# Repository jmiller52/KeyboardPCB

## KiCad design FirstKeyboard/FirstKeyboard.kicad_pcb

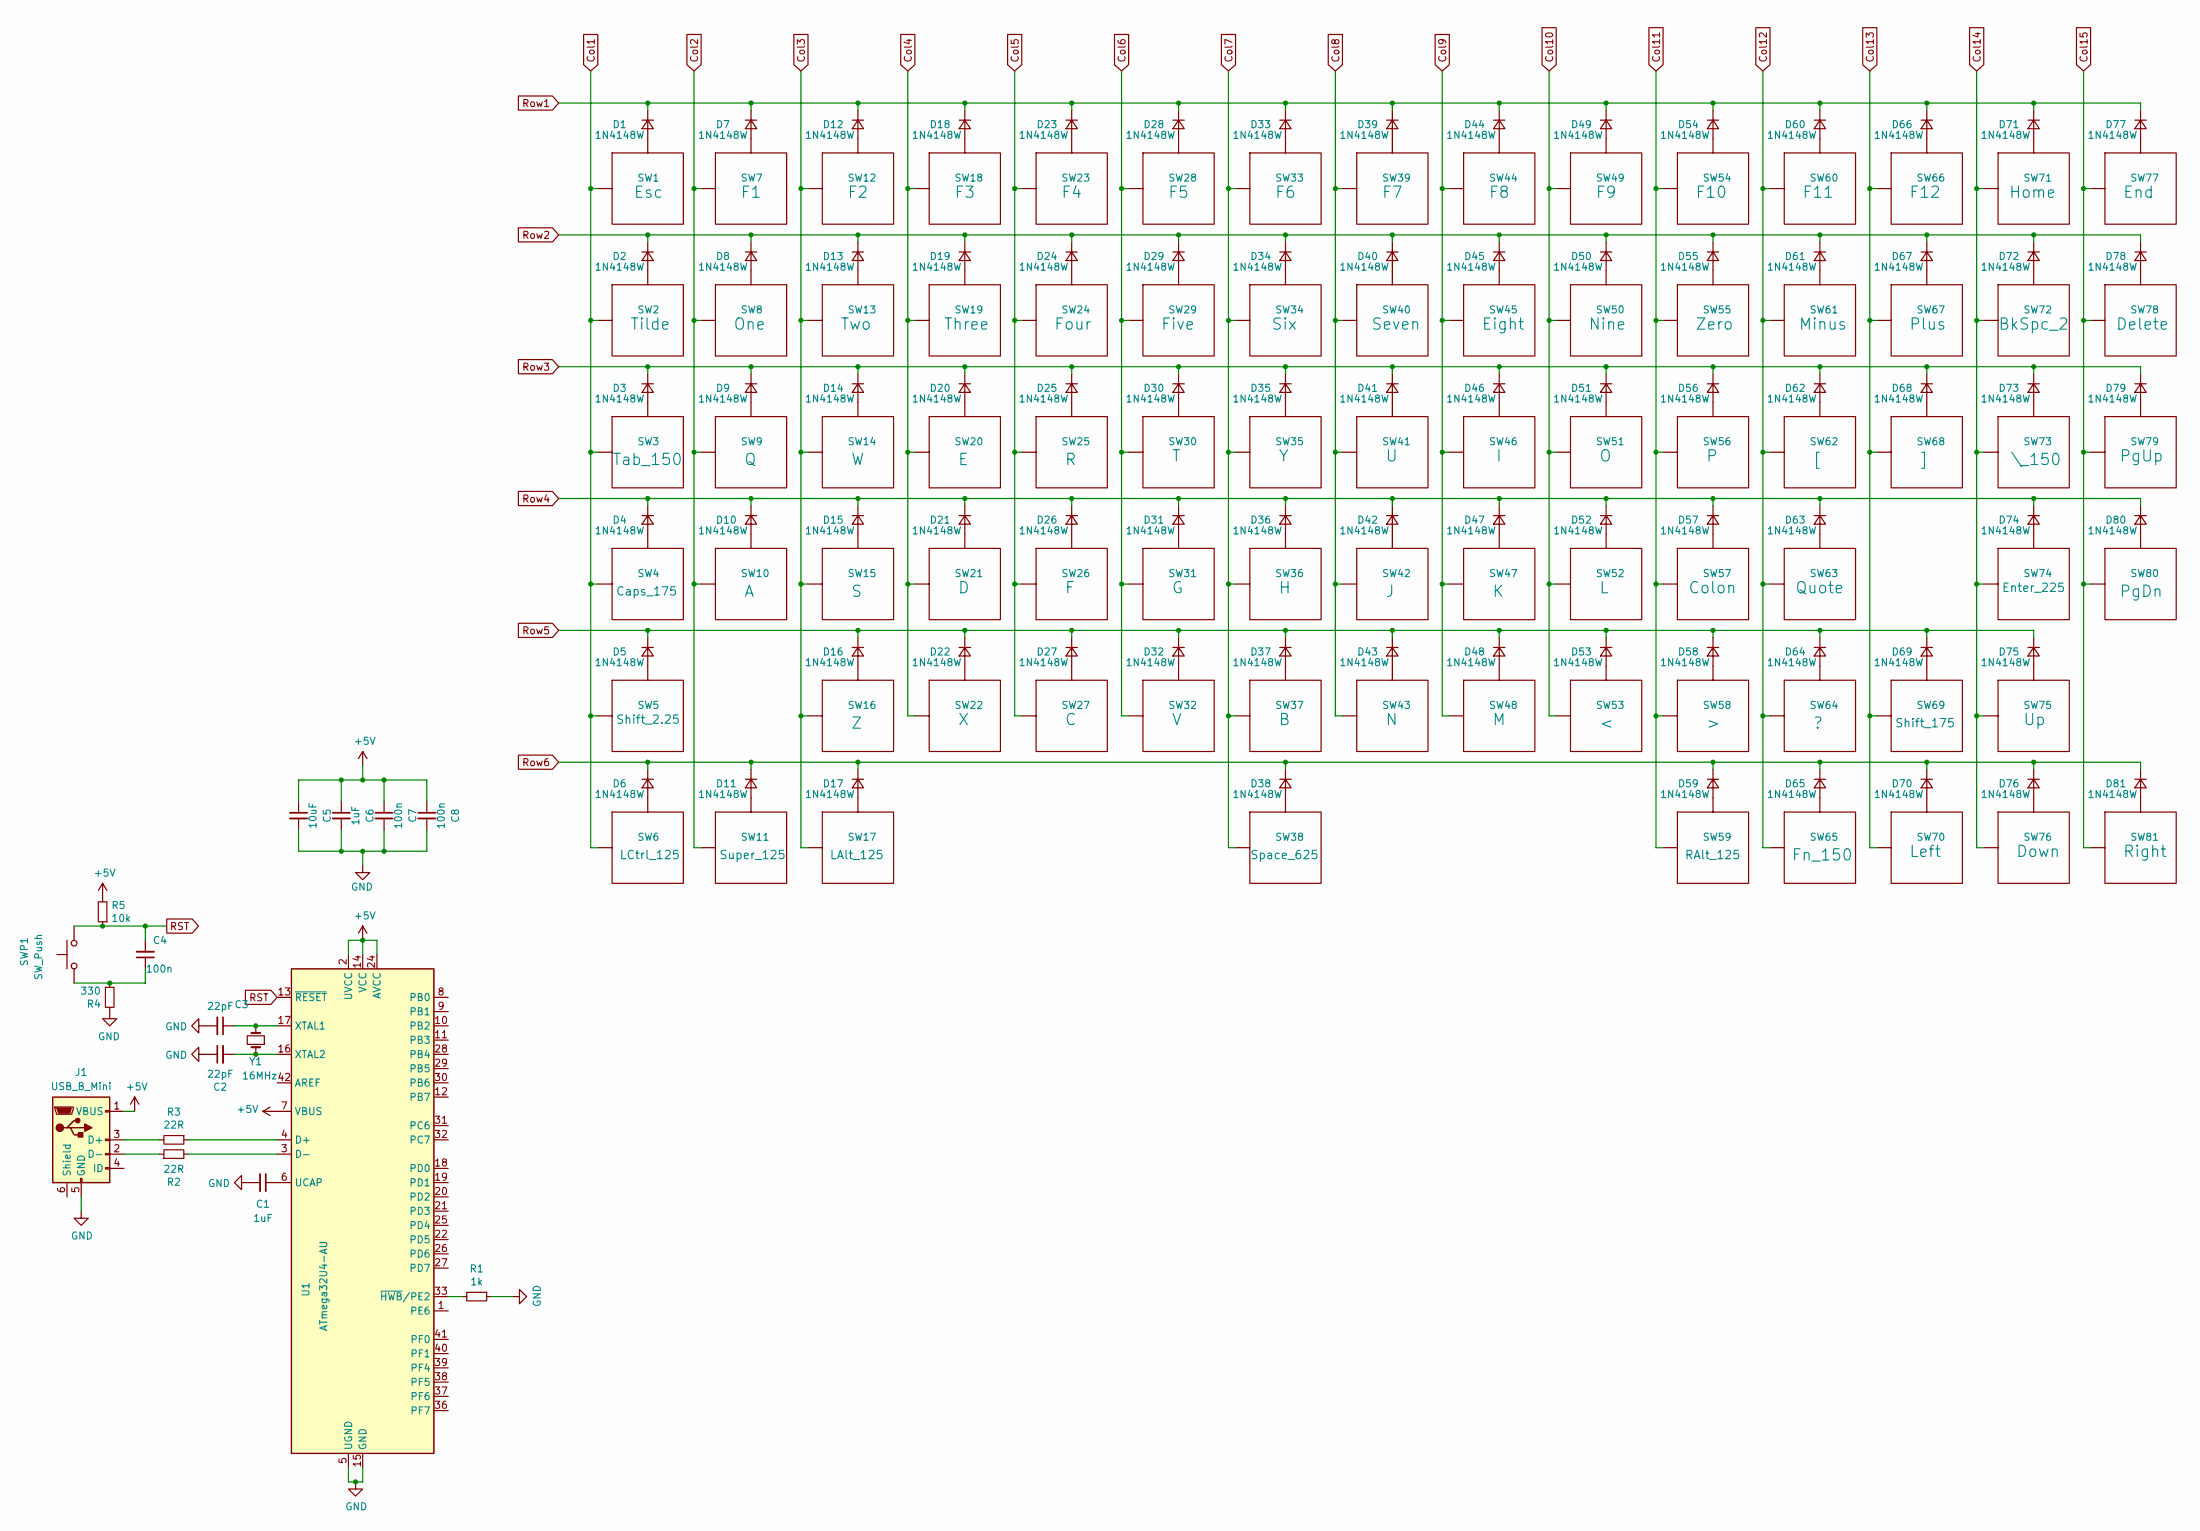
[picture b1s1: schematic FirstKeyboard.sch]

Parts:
C1, C6: 1uF; C_0805_2012Metric_Pad1.15x1.40mm_HandSolder
C2, C3: 22pF; C_0805_2012Metric_Pad1.15x1.40mm_HandSolder
C4, C7, C8: 100n; C_0805_2012Metric_Pad1.15x1.40mm_HandSolder
C5: 10uF; C_0805_2012Metric_Pad1.15x1.40mm_HandSolder
D1, D2, D3, D4, D5, D6, D7, D8, D9, D10, D11, D12, D13, D14, D15, D16, D17, D18, D19, D20, D21, D22, D23, D24, D25, D26, D27, D28, D29, D30, D31, D32, D33, D34, D35, D36, D37, D38, D39, D40, D41, D42, D43, D44, D45, D46, D47, D48, D49, D50, D51, D52, D53, D54, D55, D56, D57, D58, D59, D60, D61, D62, D63, D64, D65, D66, D67, D68, D69, D70, D71, D72, D73, D74, D75, D76, D77, D78, D79, D80, D81: 1N4148W; D_SOD-123
J1: USB_B_Mini; USB_MiniB_XM7D-0512
R1: 1k; R_1206_3216Metric_Pad1.42x1.75mm_HandSolder
R2, R3: 22R; R_1206_3216Metric_Pad1.42x1.75mm_HandSolder
R4: 330; R_1206_3216Metric_Pad1.42x1.75mm_HandSolder
R5: 10k; R_1206_3216Metric_Pad1.42x1.75mm_HandSolder
SW1: Esc; MX100P
SW2: Tilde; MX100P
SW3: Tab_150; MX150P
SW4: Caps_175; MX175P
SW5: Shift_2.25; MX225P
SW6: LCtrl_125; MX125P
SW7: F1; MX100P
SW8: One; MX100P
SW9: Q; MX100P
SW10: A; MX100P
SW11: Super_125; MX125P
SW12: F2; MX100P
SW13: Two; MX100P
SW14: W; MX100P
SW15: S; MX100P
SW16: Z; MX100P
SW17: LAlt_125; MX125P
SW18: F3; MX100P
SW19: Three; MX100P
SW20: E; MX100P
SW21: D; MX100P
SW22: X; MX100P
SW23: F4; MX100P
SW24: Four; MX100P
SW25: R; MX100P
SW26: F; MX100P
SW27: C; MX100P
SW28: F5; MX100P
SW29: Five; MX100P
SW30: T; MX100P
SW31: G; MX100P
SW32: V; MX100P
SW33: F6; MX100P
SW34: Six; MX100P
SW35: Y; MX100P
SW36: H; MX100P
SW37: B; MX100P
SW38: Space_625; MX625P
SW39: F7; MX100P
SW40: Seven; MX100P
SW41: U; MX100P
SW42: J; MX100P
SW43: N; MX100P
SW44: F8; MX100P
SW45: Eight; MX100P
SW46: I; MX100P
SW47: K; MX100P
SW48: M; MX100P
SW49: F9; MX100P
SW50: Nine; MX100P
SW51: O; MX100P
SW52: L; MX100P
SW53: <; MX100P
SW54: F10; MX100P
SW55: Zero; MX100P
SW56: P; MX100P
SW57: Colon; MX100P
SW58: >; MX100P
SW59: RAlt_125; MX125P
SW60: F11; MX100P
SW61: Minus; MX100P
SW62: [; MX100P
SW63: Quote; MX100P
SW64: ?; MX100P
SW65: Fn_150; MX150P
SW66: F12; MX100P
SW67: Plus; MX100P
SW68: ]; MX100P
SW69: Shift_175; MX175P
SW70: Left; MX100P
SW71: Home; MX100P
SW72: BkSpc_2; MX200P
SW73: \\_150; MX150P
SW74: Enter_225; MX225P
SW75: Up; MX100P
SW76: Down; MX100P
SW77: End; MX100P
SW78: Delete; MX100P
SW79: PgUp; MX100P
SW80: PgDn; MX100P
SW81: Right; MX100P
SWP1: SW_Push; smdPushBtn
U1: ATmega32U4-AU; TQFP-44_10x10mm_P0.8mm
Y1: 16MHz; Crystal_SMD_5032-2Pin_5.0x3.2mm_HandSoldering

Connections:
+5V: C5.1, C6.1, C7.1, C8.1, J1.1 (VBUS), R5.2, U1.2 (UVCC), U1.7 (VBUS), U1.14 (VCC), U1.24 (AVCC), U1.34 (VCC), U1.44 (AVCC)
Col1: SW1.1 (Col), SW2.1 (Col), SW3.1 (Col), SW4.1 (Col), SW5.1 (Col), SW6.1 (Col)
Col2: SW7.1 (Col), SW8.1 (Col), SW9.1 (Col), SW10.1 (Col), SW11.1 (Col)
Col3: SW12.1 (Col), SW13.1 (Col), SW14.1 (Col), SW15.1 (Col), SW16.1 (Col), SW17.1 (Col)
Col4: SW18.1 (Col), SW19.1 (Col), SW20.1 (Col), SW21.1 (Col), SW22.1 (Col)
Col5: SW23.1 (Col), SW24.1 (Col), SW25.1 (Col), SW26.1 (Col), SW27.1 (Col)
Col6: SW28.1 (Col), SW29.1 (Col), SW30.1 (Col), SW31.1 (Col), SW32.1 (Col)
Col7: SW33.1 (Col), SW34.1 (Col), SW35.1 (Col), SW36.1 (Col), SW37.1 (Col), SW38.1 (Col)
Col8: SW39.1 (Col), SW40.1 (Col), SW41.1 (Col), SW42.1 (Col), SW43.1 (Col)
Col9: SW44.1 (Col), SW45.1 (Col), SW46.1 (Col), SW47.1 (Col), SW48.1 (Col)
Col10: SW49.1 (Col), SW50.1 (Col), SW51.1 (Col), SW52.1 (Col), SW53.1 (Col)
Col11: SW54.1 (Col), SW55.1 (Col), SW56.1 (Col), SW57.1 (Col), SW58.1 (Col), SW59.1 (Col)
Col12: SW60.1 (Col), SW61.1 (Col), SW62.1 (Col), SW63.1 (Col), SW64.1 (Col), SW65.1 (Col)
Col13: SW66.1 (Col), SW67.1 (Col), SW68.1 (Col), SW69.1 (Col), SW70.1 (Col)
Col14: SW71.1 (Col), SW72.1 (Col), SW73.1 (Col), SW74.1 (Col), SW75.1 (Col), SW76.1 (Col)
Col15: SW77.1 (Col), SW78.1 (Col), SW79.1 (Col), SW80.1 (Col), SW81.1 (Col)
GND: C1.2, C2.1, C3.2, C5.2, C6.2, C7.2, C8.2, J1.5 (GND), R1.1, R4.2, U1.5 (UGND), U1.15 (GND), U1.23 (GND), U1.35 (GND), U1.43 (GND)
unnamed: C1.1, U1.6 (UCAP)
unnamed: C2.2, U1.16 (XTAL2), Y1.1
unnamed: C3.1, U1.17 (XTAL1), Y1.2
unnamed: C4.1, R4.1, SWP1.1
unnamed: D1.2 (A), SW1.2 (Row)
unnamed: D2.2 (A), SW2.2 (Row)
unnamed: D3.2 (A), SW3.2 (Row)
unnamed: D4.2 (A), SW4.2 (Row)
unnamed: D5.2 (A), SW5.2 (Row)
unnamed: D6.2 (A), SW6.2 (Row)
unnamed: D7.2 (A), SW7.2 (Row)
unnamed: D8.2 (A), SW8.2 (Row)
unnamed: D9.2 (A), SW9.2 (Row)
unnamed: D10.2 (A), SW10.2 (Row)
unnamed: D11.2 (A), SW11.2 (Row)
unnamed: D12.2 (A), SW12.2 (Row)
unnamed: D13.2 (A), SW13.2 (Row)
unnamed: D14.2 (A), SW14.2 (Row)
unnamed: D15.2 (A), SW15.2 (Row)
unnamed: D16.2 (A), SW16.2 (Row)
unnamed: D17.2 (A), SW17.2 (Row)
unnamed: D18.2 (A), SW18.2 (Row)
unnamed: D19.2 (A), SW19.2 (Row)
unnamed: D20.2 (A), SW20.2 (Row)
unnamed: D21.2 (A), SW21.2 (Row)
unnamed: D22.2 (A), SW22.2 (Row)
unnamed: D23.2 (A), SW23.2 (Row)
unnamed: D24.2 (A), SW24.2 (Row)
unnamed: D25.2 (A), SW25.2 (Row)
unnamed: D26.2 (A), SW26.2 (Row)
unnamed: D27.2 (A), SW27.2 (Row)
unnamed: D28.2 (A), SW28.2 (Row)
unnamed: D29.2 (A), SW29.2 (Row)
unnamed: D30.2 (A), SW30.2 (Row)
unnamed: D31.2 (A), SW31.2 (Row)
unnamed: D32.2 (A), SW32.2 (Row)
unnamed: D33.2 (A), SW33.2 (Row)
unnamed: D34.2 (A), SW34.2 (Row)
unnamed: D35.2 (A), SW35.2 (Row)
unnamed: D36.2 (A), SW36.2 (Row)
unnamed: D37.2 (A), SW37.2 (Row)
unnamed: D38.2 (A), SW38.2 (Row)
unnamed: D39.2 (A), SW39.2 (Row)
unnamed: D40.2 (A), SW40.2 (Row)
unnamed: D41.2 (A), SW41.2 (Row)
unnamed: D42.2 (A), SW42.2 (Row)
unnamed: D43.2 (A), SW43.2 (Row)
unnamed: D44.2 (A), SW44.2 (Row)
unnamed: D45.2 (A), SW45.2 (Row)
unnamed: D46.2 (A), SW46.2 (Row)
unnamed: D47.2 (A), SW47.2 (Row)
unnamed: D48.2 (A), SW48.2 (Row)
unnamed: D49.2 (A), SW49.2 (Row)
unnamed: D50.2 (A), SW50.2 (Row)
unnamed: D51.2 (A), SW51.2 (Row)
unnamed: D52.2 (A), SW52.2 (Row)
unnamed: D53.2 (A), SW53.2 (Row)
unnamed: D54.2 (A), SW54.2 (Row)
unnamed: D55.2 (A), SW55.2 (Row)
unnamed: D56.2 (A), SW56.2 (Row)
unnamed: D57.2 (A), SW57.2 (Row)
unnamed: D58.2 (A), SW58.2 (Row)
unnamed: D59.2 (A), SW59.2 (Row)
unnamed: D60.2 (A), SW60.2 (Row)
unnamed: D61.2 (A), SW61.2 (Row)
unnamed: D62.2 (A), SW62.2 (Row)
unnamed: D63.2 (A), SW63.2 (Row)
unnamed: D64.2 (A), SW64.2 (Row)
unnamed: D65.2 (A), SW65.2 (Row)
unnamed: D66.2 (A), SW66.2 (Row)
unnamed: D67.2 (A), SW67.2 (Row)
unnamed: D68.2 (A), SW68.2 (Row)
unnamed: D69.2 (A), SW69.2 (Row)
unnamed: D70.2 (A), SW70.2 (Row)
unnamed: D71.2 (A), SW71.2 (Row)
unnamed: D72.2 (A), SW72.2 (Row)
unnamed: D73.2 (A), SW73.2 (Row)
unnamed: D74.2 (A), SW74.2 (Row)
unnamed: D75.2 (A), SW75.2 (Row)
unnamed: D76.2 (A), SW76.2 (Row)
unnamed: D77.2 (A), SW77.2 (Row)
unnamed: D78.2 (A), SW78.2 (Row)
unnamed: D79.2 (A), SW79.2 (Row)
unnamed: D80.2 (A), SW80.2 (Row)
unnamed: D81.2 (A), SW81.2 (Row)
unnamed: J1.2 (D-), R2.1
unnamed: J1.3 (D+), R3.2
unnamed: R1.2, U1.33 (~HWB~/PE2)
unnamed: R2.2, U1.3 (D-)
unnamed: R3.1, U1.4 (D+)
RST: C4.2, R5.1, SWP1.2, U1.13 (~RESET)
Row1: D1.1 (K), D7.1 (K), D12.1 (K), D18.1 (K), D23.1 (K), D28.1 (K), D33.1 (K), D39.1 (K), D44.1 (K), D49.1 (K), D54.1 (K), D60.1 (K), D66.1 (K), D71.1 (K), D77.1 (K)
Row2: D2.1 (K), D8.1 (K), D13.1 (K), D19.1 (K), D24.1 (K), D29.1 (K), D34.1 (K), D40.1 (K), D45.1 (K), D50.1 (K), D55.1 (K), D61.1 (K), D67.1 (K), D72.1 (K), D78.1 (K)
Row3: D3.1 (K), D9.1 (K), D14.1 (K), D20.1 (K), D25.1 (K), D30.1 (K), D35.1 (K), D41.1 (K), D46.1 (K), D51.1 (K), D56.1 (K), D62.1 (K), D68.1 (K), D73.1 (K), D79.1 (K)
Row4: D4.1 (K), D10.1 (K), D15.1 (K), D21.1 (K), D26.1 (K), D31.1 (K), D36.1 (K), D42.1 (K), D47.1 (K), D52.1 (K), D57.1 (K), D63.1 (K), D74.1 (K), D80.1 (K)
Row5: D5.1 (K), D16.1 (K), D22.1 (K), D27.1 (K), D32.1 (K), D37.1 (K), D43.1 (K), D48.1 (K), D53.1 (K), D58.1 (K), D64.1 (K), D69.1 (K), D75.1 (K)
Row6: D6.1 (K), D11.1 (K), D17.1 (K), D38.1 (K), D59.1 (K), D65.1 (K), D70.1 (K), D76.1 (K), D81.1 (K)

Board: 2 copper layers, 179 parts (177 on the bottom side), 114 nets, no tracks yet.

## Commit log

2019-12-04 Adding Keyboard docs to github
2019-12-04 Adding
2019-12-06 A little more done
2019-12-09 Morning Updates Dec9
2019-12-09 added gitignore and other files
2019-12-09 Last update of the day
2019-12-10 updated git ignore
2019-12-10 updated gitignore for Windows
2019-12-10 Real update, Removed files that needed ignore
2019-12-10 Dec10 Update, Starting full board
2019-12-11 Finished Scematic?
2019-12-11 Finished Schematic?
2019-12-11 Removed the "INS" key
2019-12-11 Small update to Aly keys
2019-12-11 Updating the keyboard layout
2019-12-11 Keys are in place. Next diodes?
2019-12-16 Re-added pcb cut edge
2019-12-16 Adding Acheron Library and My updates
2019-12-16 Staging again
2019-12-16 updated assigned footprints and pcb from Schema
